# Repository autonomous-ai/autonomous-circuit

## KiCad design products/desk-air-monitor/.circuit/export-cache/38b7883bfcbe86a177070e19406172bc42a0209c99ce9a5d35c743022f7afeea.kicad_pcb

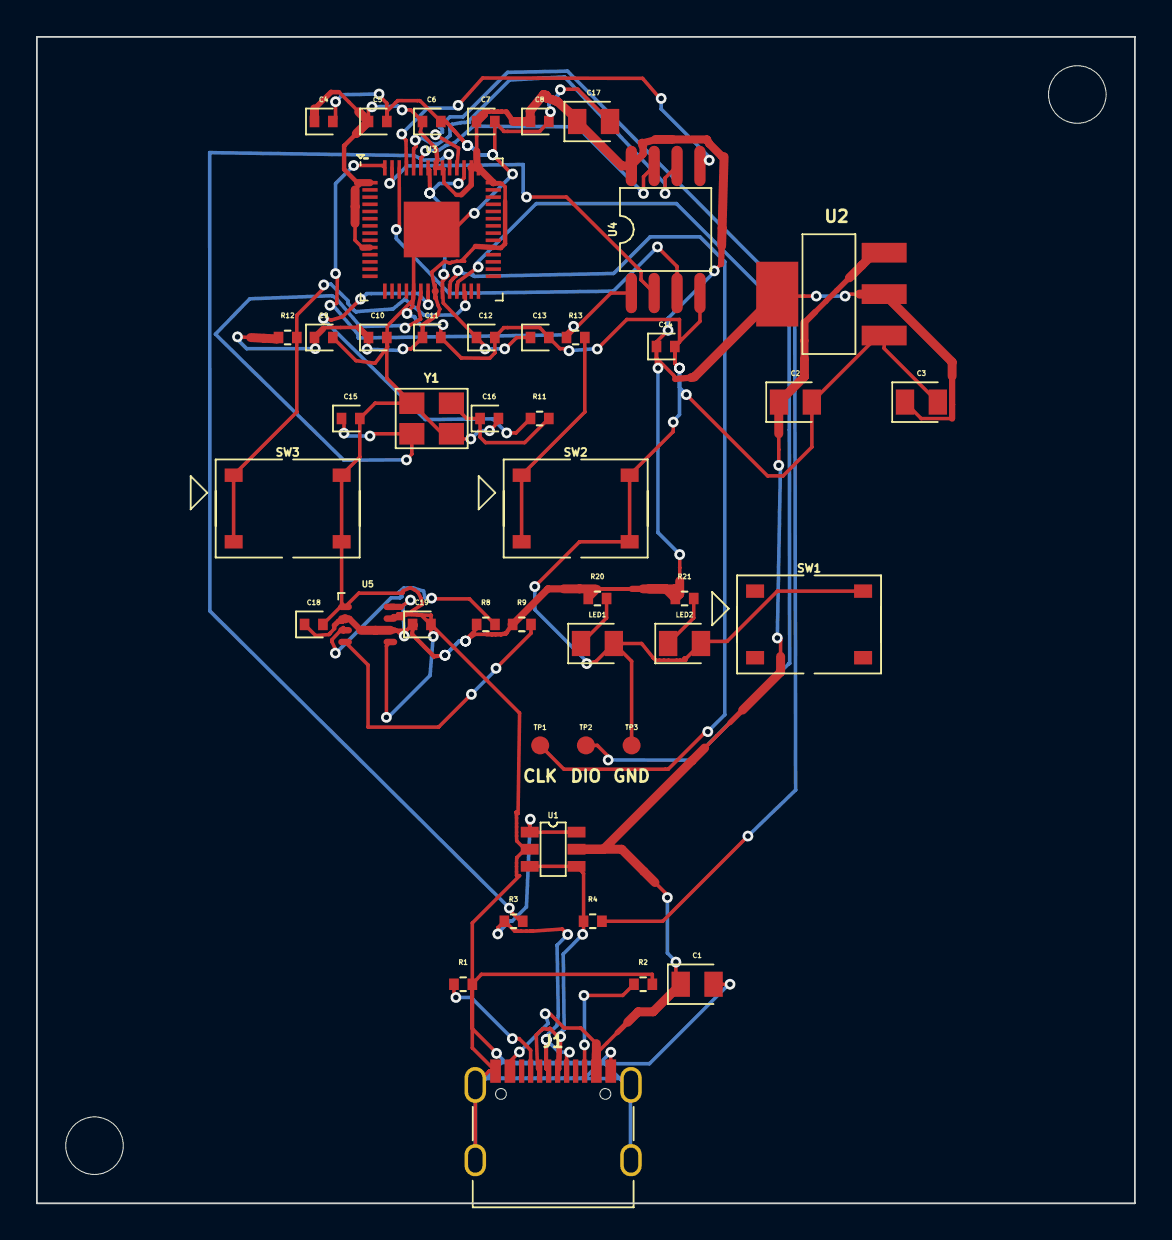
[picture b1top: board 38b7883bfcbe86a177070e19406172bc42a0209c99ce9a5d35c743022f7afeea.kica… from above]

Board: 2 copper layers, 61.0 x 64.8 mm, 45 parts (0 on the bottom side), 27 nets.

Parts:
C1, C2, C3, C17: 10uF; capacitor_cap0805
C4, C5, C6, C7, C8, C9, C10, C11, C13, C14, C18, C19: 100nF; capacitor_cap0402
C12: 1uF; capacitor_cap0402
C15, C16: 15pF; capacitor_cap0402
J1: J1; TYPE-C-31-M-12
LED1, LED2: LED; led_0805_color(green)
R1, R2: 5.1kΩ; resistor_res0402
R3, R4: 27Ω; resistor_res0402
R8, R9: 4.7kΩ; resistor_res0402
R11, R13, R20, R21: 1kΩ; resistor_res0402
R12: 10kΩ; resistor_res0402
SW1: SW1; push_button_dfn4_p3.6998mm_w7mm_pw0.75mm
SW2: SW2; push_button_dfn4_p3.6998mm_w7mm_pw0.75mm
SW3: SW3; push_button_dfn4_p3.6998mm_w7mm_pw0.75mm
TP1: TP1; test_point_smtpad_circle_d1
TP2: TP2; test_point_smtpad_circle_d1
TP3: TP3; test_point_smtpad_circle_d1
U1: USBLC6-2SC6
U2: AMS1117-3.3
U3: RP2040
U4: W25Q128JVSIQ
U5: BME280
Y1: Y1; crystal_crystal

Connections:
.J1 > .CC1 to .R1 > .pin1: J1.6, R1.1
.J1 > .CC2 to .R2 > .pin1: J1.12, R2.1
.R11 > .pin2 to .Y1 > .pin3: C16.1, R11.2, Y1.3
.R20 > .pin2 to .LED1 > .anode: LED1.1, R20.2
.R21 > .pin2 to .LED2 > .anode: LED2.1, R21.2
.U3 > .XOUT to .R11 > .pin1: R11.1, U3.21
.U4 > .CLK to .U3 > .QSPI_SCLK: U3.52, U4.6
.U4 > .CS to .U3 > .QSPI_SS: R13.1, U3.56, U4.1
.U4 > .IO0 to .U3 > .QSPI_SD0: U3.53, U4.5
.U4 > .IO1 to .U3 > .QSPI_SD1: U3.55, U4.2
.U4 > .IO2 to .U3 > .QSPI_SD2: U3.54, U4.3
.U4 > .IO3 to .U3 > .QSPI_SD3: U3.51, U4.7
.Y1 > .pin1 to .U3 > .XIN: C15.1, U3.20, Y1.1
BOOTSEL_SW: R13.2, SW2.1, SW2.2
DVDD: C12.1, C13.1, U3.23, U3.45, U3.50
GND: C1.2, C2.2, C3.2, C4.2, C5.2, C6.2, C7.2, C8.2, C9.2, C10.2, C11.2, C12.2, C13.2, C14.2, C15.2, C16.2, C17.2, C18.2, C19.2, J1.1, J1.2, J1.3, J1.4, J1.13, J1.14, LED1.2, LED2.2, R1.2, R2.2, SW1.4, SW2.3, SW2.4, SW3.3, SW3.4, TP3.1, U1.2, U2.1, U3.19, U3.57, U4.4, U5.1, U5.5, U5.7, Y1.2, Y1.4
RUN_SW: R12.2, SW3.1, SW3.2, U3.26
SCL: R9.2, U5.4
SDA: R8.2, U5.3
SWCLK: TP1.1, U3.24
SWD: TP2.1, U3.25
USB_DM: R4.2, U3.46
USB_DM_CONN: J1.7, J1.9, R4.1, U1.3, U1.4
USB_DP: R3.2, U3.47
USB_DP_CONN: J1.8, J1.10, R3.1, U1.1, U1.6
V3_3: C3.1, C4.1, C5.1, C6.1, C7.1, C8.1, C9.1, C10.1, C11.1, C14.1, C17.1, C18.1, C19.1, R8.1, R9.1, R12.1, R20.1, R21.1, U2.2, U2.4, U3.1, U3.10, U3.22, U3.33, U3.42, U3.43, U3.44, U3.48, U3.49, U4.8, U5.2, U5.6, U5.8
V5: C1.1, C2.1, J1.15, J1.16, U1.5, U2.3

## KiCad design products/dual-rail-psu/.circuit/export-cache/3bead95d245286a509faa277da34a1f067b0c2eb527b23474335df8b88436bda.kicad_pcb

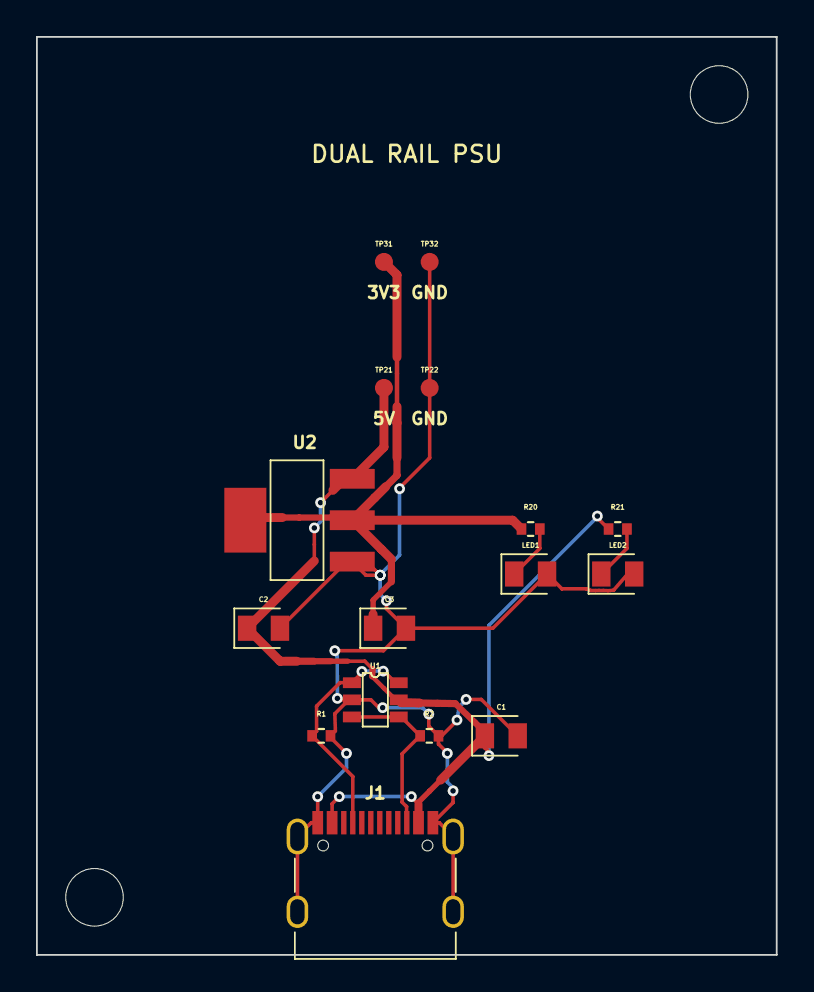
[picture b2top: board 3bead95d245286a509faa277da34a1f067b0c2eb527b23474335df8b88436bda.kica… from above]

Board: 2 copper layers, 41.1 x 51.0 mm, 16 parts (0 on the bottom side), 7 nets.

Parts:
C1, C2, C3: 10uF; capacitor_cap0805
J1: J1; TYPE-C-31-M-12
LED1, LED2: LED; led_0805_color(green)
R1, R2: 5.1kΩ; resistor_res0402
R20, R21: 1kΩ; resistor_res0402
TP21: TP21; test_point_smtpad_circle_d1
TP22: TP22; test_point_smtpad_circle_d1
TP31: TP31; test_point_smtpad_circle_d1
TP32: TP32; test_point_smtpad_circle_d1
U1: USBLC6-2SC6
U2: AMS1117-3.3

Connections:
.J1 > .CC1 to .R1 > .pin1: J1.6, R1.1, U1.1, U1.6
.J1 > .CC2 to .R2 > .pin1: J1.12, R2.1, U1.3, U1.4
.R20 > .pin2 to .LED1 > .anode: LED1.1, R20.2
.R21 > .pin2 to .LED2 > .anode: LED2.1, R21.2
GND: C1.2, C2.2, C3.2, J1.1, J1.2, J1.3, J1.4, J1.13, J1.14, LED1.2, LED2.2, R1.2, R2.2, TP22.1, TP32.1, U1.2, U2.1
V3_3: C3.1, R20.1, TP31.1, U2.2, U2.4
V5: C1.1, C2.1, J1.15, J1.16, R21.1, TP21.1, U1.5, U2.3
